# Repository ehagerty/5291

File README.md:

#  All original rights to manisteinn from Deskthority...

readme copied from https://github.com/qmk/qmk_firmware/tree/master/keyboards/converter/ibm_5291

# IBM 5291 keyboard converter

[IBM 5291](https://deskthority.net/wiki/IBM_Model_F#IBM_5291_Keyboard)

A converter for the eponymous keyboard.

Keyboard Maintainer: [Listofoptions](https://github.com/listofoptions)
Hardware Supported: IBM 5291, Teensy 2.0

Make example for this keyboard (after setting up your build environment):

    make converter/ibm_5291:default

See the [build environment setup](https://docs.qmk.fm/#/getting_started_build_tools) and the [make instructions](https://docs.qmk.fm/#/getting_started_make_guide) for more information. Brand new to QMK? Start with our [Complete Newbs Guide](https://docs.qmk.fm/#/newbs).

The pinout is as follows:

IBM−5291−Cable to Pinhead−14

| pin | description |
| --- | ----------- |
| 1   | GND         |
| 2   | NC          |
| 3   | GND         |
| 4   | GN)         |
| 5   | +5V         |
| 6   | D0          |
| 7   | D1          |
| 8   | D2          |
| 9   | D3          |
| 10  | D4          |
| 11  | D5          |
| 12  | D6          |
| 13  | Strobe      |
| 14  | Out         |

The pins on this connector are organized

IBM−5291−2 Cable with DB15M connector

| pin   | description |
| ----- | ----------- |
| 1,2,3 | GND         |
| 4     | +5V         |
| 5     | D0          |
| 6     | D1          |
| 7     | D2          |
| 8     | D3          |
| 9     | D4          |
| 10    | D5          |
| 11    | D6          |
| 12    | Strobe      |
| 13    | Out         |
| 14    | PE          |
| 15    | NC          |

The above connector is actually numbered so it should be easier to determine
where the needed connections are.

To connect to the teensy, the following are pins are needed (if you should choose not set your own):

- PB0 -> PB6 are connected to D0 -> D6
- +5V is connected to the corresponding teensy pin
- gnd is as well, only one of the gnd pins needs to be connected though.
- strobe is connected to pin PD1
- data is connected to PD0
- PE does not need to be connected to anything, but it could also be connected to gnd

sources:
http://www.retrocomputing.eu/documents/5291_MaintenanceLibrary.pdf

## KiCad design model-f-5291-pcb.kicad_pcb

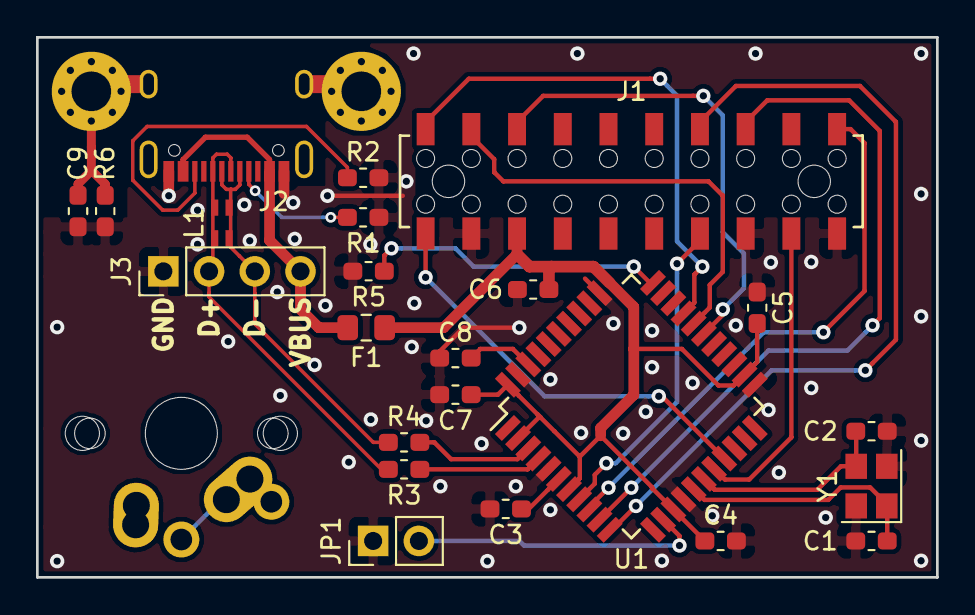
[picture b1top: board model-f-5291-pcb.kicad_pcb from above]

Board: 2 copper layers, 50.0 x 30.0 mm, 26 parts (0 on the bottom side), 25 nets.

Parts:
C1, C2: 18p; C_0603_1608Metric_Pad1.05x0.95mm_HandSolder
C3: 1u; C_0603_1608Metric_Pad1.05x0.95mm_HandSolder
C4, C5, C6, C7, C8, C9: 0.1u; C_0603_1608Metric_Pad1.05x0.95mm_HandSolder
F1: Polyfuse; Fuse_0805_2012Metric_Pad1.15x1.40mm_HandSolder
J1: Keyboard; Harwin-M20-7811045
J2: USB_C_Receptacle; USB_TypeC_U31F-24SNA0201
J3: USB; PinHeader_1x04_P2.54mm_Vertical
JP1: Jumper_NO_Small; PinHeader_1x02_P2.54mm_Vertical
L1: DLW21SN900SQ2L; DLW21
MH1, MH2: MountingHole_Pad; MountingHole_2.2mm_M2_Pad_Via
R1, R2: 5.1K; R_0603_1608Metric_Pad1.05x0.95mm_HandSolder
R3, R4: 22; R_0603_1608Metric_Pad1.05x0.95mm_HandSolder
R5: 1K; R_0603_1608Metric_Pad1.05x0.95mm_HandSolder
R6: 330; R_0603_1608Metric_Pad1.05x0.95mm_HandSolder
SW1: SW_SPST; MX_Matias_KailhLP_NoSilk
U1: ATmega32U4-AU; TQFP-44_10x10mm_P0.8mm
Y1: Crystal_GND24; Crystal_SMD_3225-4Pin_3.2x2.5mm

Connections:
+5V: C4.1, C5.1, C6.1, C7.1, F1.1, J1.13, U1.2, U1.7, U1.14, U1.24, U1.34, U1.44
/CC1: J2.A5, R1.1
/CC2: J2.B5, R2.1
/Count1: J1.17, U1.8
/Count2: J1.1, U1.9
/Count4: J1.3, U1.10
/Count8: J1.4, U1.11
/Count16: J1.8, U1.28
/Count32: J1.9, U1.29
/Count64: J1.10, U1.30
/D+: J2.A6, J2.B6, J3.2, L1.1, L1.2, R3.1
/D-: J2.A7, J2.B7, J3.3, L1.3, L1.4, R4.1
/Key_Depressed: J1.11, U1.19
/Matrix_Strobe: J1.19, U1.18
/Shield: C9.1, J2.S1, MH1.1, MH2.1, R6.1
/VBUS_CON: F1.2, J2.A4, J2.B4, J3.4
/~RESET: JP1.2, U1.13
GND: C1.2, C2.2, C3.2, C4.2, C5.2, C6.2, C7.2, C8.2, C9.2, J1.12, J1.18, J1.20, J2.A1, J2.B1, J3.1, JP1.1, R1.2, R2.2, R5.1, R6.2, U1.5, U1.15, U1.23, U1.35, U1.43, Y1.2, Y1.4
unnamed: C1.1, U1.16, Y1.1
unnamed: C2.1, U1.17, Y1.3
unnamed: C3.1, U1.6
unnamed: C8.1, U1.42
unnamed: R3.2, U1.4
unnamed: R4.2, U1.3
unnamed: R5.2, U1.33

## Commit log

2021-06-09 initial
